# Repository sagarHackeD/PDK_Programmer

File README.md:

# PDK_Programmer
PADUK_Programmer

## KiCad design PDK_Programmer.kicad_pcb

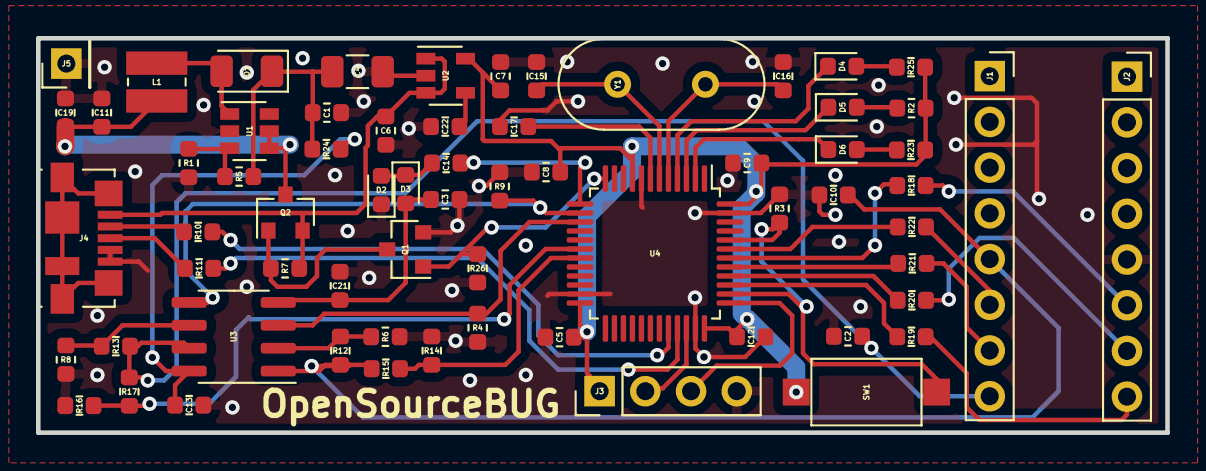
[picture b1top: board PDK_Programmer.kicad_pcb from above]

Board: 2 copper layers, 62.7 x 21.9 mm, 66 parts (0 on the bottom side), 48 nets.

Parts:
C1: 100uF; C_0603_1608Metric
C2, C5, C8, C9, C10, C12, C14, C17, C19, C22: 100nF; C_0603_1608Metric
C3: 100nf; C_0603_1608Metric
C4: 47uF; C_1206_3216Metric
C6, C7, C11, C13, C21: 4.7uF; C_0603_1608Metric
C15, C16: 20pF; C_0603_1608Metric
D1: Schottky; D_1206_3216Metric
D2, D3: D; D_0603_1608Metric
D4, D5, D6: LED; LED_0603_1608Metric
J1, J2: Conn_01x08_Female; PinSocket_1x08_P2.54mm_Vertical
J3: SWD; PinHeader_1x04_P2.54mm_Vertical
J4: USB_B_Micro; USB_Micro-B_Molex_47346-0001
J5: Conn_01x01_Male; PinHeader_1x01_P2.54mm_Vertical
L1: 6.8uH; L_Wuerth_MAPI-3015
Q1: BSS138; SOT-23
Q2: BSS84; SOT-23
R1: 10K; R_0603_1608Metric
R2, R23, R25: 1K; R_0603_1608Metric
R3, R6, R12, R13, R14, R16: 20K; R_0603_1608Metric
R4, R5, R9, R26: 240K; R_0603_1608Metric
R7, R8: 6.2K; R_0603_1608Metric
R10, R11, R24: 20R; R_0603_1608Metric
R15, R17: 100K; R_0603_1608Metric
R18, R19, R20, R21, R22: 100R; R_0603_1608Metric
SW1: SW; SW_SPST_CK_RS282G05A3
U1: MT3608; SOT-23-6
U2: LP2985-3.3; SOT-23-5
U3: LM358; SOIC-8_3.9x4.9mm_P1.27mm
U4: STM32F072C8Tx; LQFP-48_7x7mm_P0.5mm
Y1: 8MHz; Crystal_HC49-4H_Vertical

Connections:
+3V3: C5.1, C7.1, C8.1, C9.1, C12.1, J3.1, R2.1, R23.1, R25.1, SW1.1, U2.5 (VOUT), U4.9 (VDDA), U4.24 (VDD), U4.36 (VDDIO2), U4.48 (VDD)
+5V: C6.1, J4.1 (VBUS), Q2.2 (S), R7.2, U2.1 (VIN), U2.3 (ON/~OFF~)
+15V: C1.1, C4.1, D1.1 (K), R5.1, R24.1
/BOOST_EN: Q1.1 (G), R26.1, U4.12 (PA2)
/D+: R11.2, U4.33 (PA12)
/D-: R10.1, U4.32 (PA11)
/PA0: J2.6, R18.2
/PA3_ICPCK: J2.8, R19.2
/PA4: J2.7, R20.2
/PA6_ICPDA: J1.7, R21.2
/PA7: J1.6, R22.2
/VCC: C10.1, J1.5, R12.1, R15.1, U3.1
/VCC_ADJ: R4.1, U3.3 (+), U4.15 (PA5)
/VCC_FEEDBACK: R14.1, R15.2, U4.19 (PB1)
/VOLTAGE_MULTI: C14.2, U4.13 (PA3)
/VPP: C2.1, J1.8, R13.1, R17.1, U3.7
/VPP_ADJ: R9.1, U3.5 (+), U4.14 (PA4)
/VPP_FEEDBACK: R16.1, R17.2, U4.18 (PB0)
BOOT0: R3.1, SW1.2, U4.38 (PA15), U4.44 (BOOT0)
GND: C1.2, C2.2, C3.2, C4.2, C5.2, C6.2, C7.2, C8.2, C9.2, C10.2, C11.2, C12.2, C13.2, C15.2, C16.2, C17.2, C19.2, C21.2, C22.2, D2.1 (K), J2.5, J3.4, J4.4 (ID), J4.5 (GND), J5.1, Q1.2 (S), R1.2, R3.2, R4.2, R6.2, R8.2, R9.2, R14.2, R16.2, R26.2, U1.2 (GND), U2.2 (GND), U4.8 (VSSA), U4.23 (VSS), U4.35 (VSS), U4.47 (VSS)
unnamed: C11.1, C19.1, L1.1, Q2.3 (D), U1.4 (EN), U1.5 (IN)
unnamed: C13.1, R24.2, U3.8 (V+)
unnamed: C14.1, D2.2 (A), D3.1 (K)
unnamed: C17.1, U4.7 (NRST)
unnamed: C3.1, C21.1, D3.2 (A), U3.4 (V-)
unnamed: C22.1, U2.4 (BP)
unnamed: D1.2 (A), L1.2, U1.1 (SW)
unnamed: D4.2 (A), R25.2
unnamed: D5.2 (A), R2.2
unnamed: D6.2 (A), R23.2
unnamed: J4.2 (D-), R10.2
unnamed: J4.3 (D+), R11.1
unnamed: Q1.3 (D), Q2.1 (G), R7.1
unnamed: R1.1, R5.2, U1.3 (FB)
unnamed: R6.1, R12.2, U3.2 (-)
unnamed: R8.1, R13.2, U3.6 (-)
unnamed: R18.1, U4.42 (PB6)
unnamed: R19.1, U4.39 (PB3)
unnamed: R20.1, U4.40 (PB4)
unnamed: R21.1, U4.41 (PB5)
unnamed: R22.1, U4.43 (PB7)
PC13: D6.1 (K), U4.2 (PC13)
PC14: D5.1 (K), U4.3 (PC14)
PC15: D4.1 (K), U4.4 (PC15)
SWCLK: J3.3, U4.37 (PA14)
SWDIO: J3.2, U4.34 (PA13)
XTAL1: C16.1, U4.5 (PF0), Y1.2
XTAL2: C15.1, U4.6 (PF1), Y1.1
